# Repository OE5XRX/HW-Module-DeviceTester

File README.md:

# HW-Module-DeviceTester

## License

This project is licensed under [CERN-OHL-S-2.0](https://choosealicense.com/licenses/cern-ohl-s-2.0/).

## Badges

<br>
<br>
<br>
<br>
<br>

## Contact

OE5XRX Amateur Radio Club<br>
🌐 https://oe5xrx.org<br>
✉️ info@oe5xrx.org<br>

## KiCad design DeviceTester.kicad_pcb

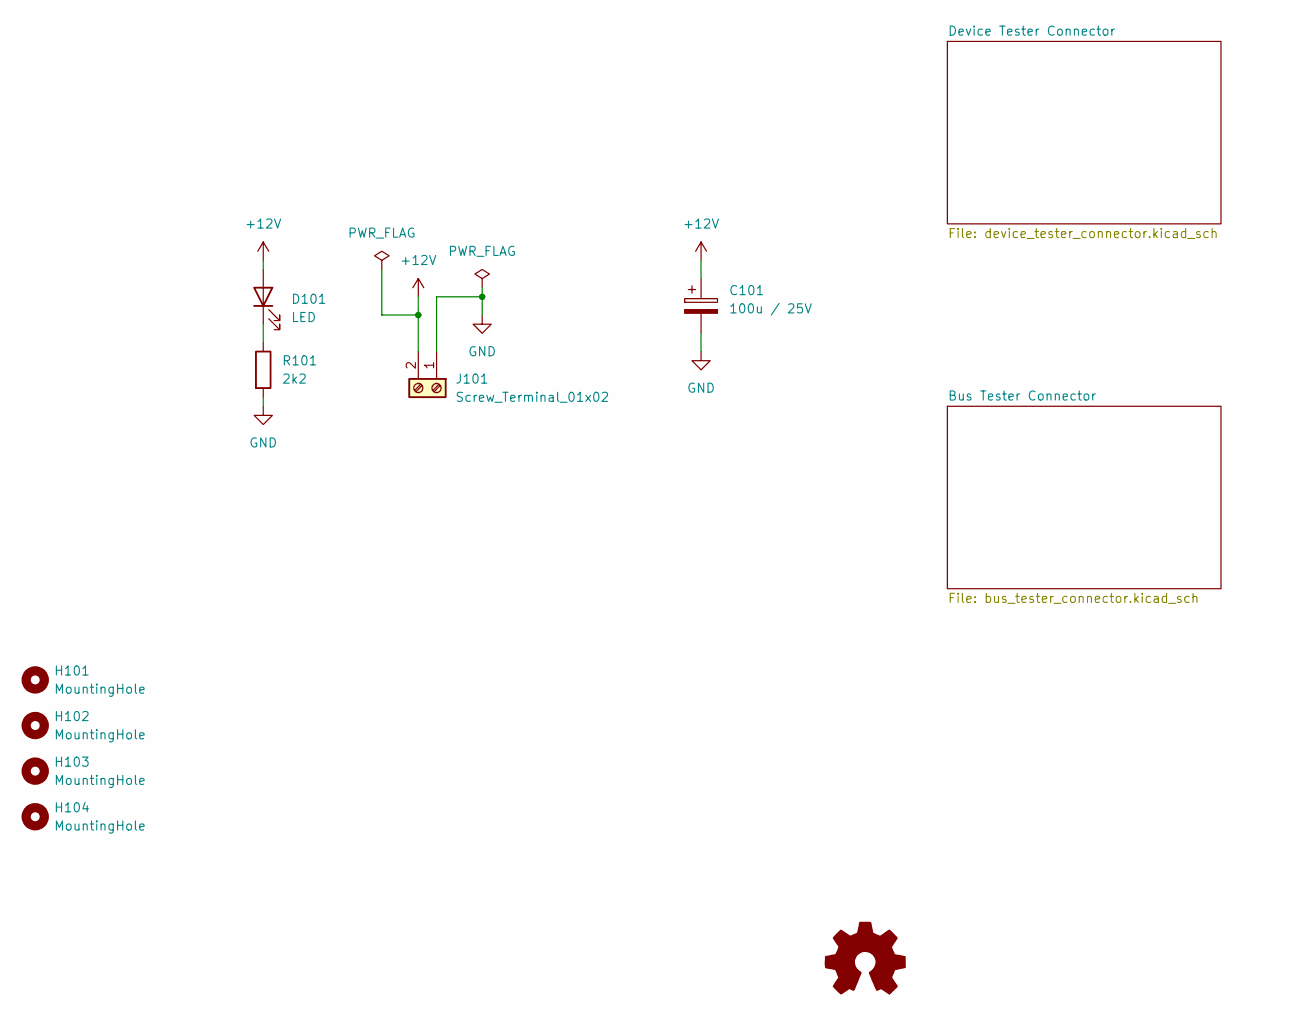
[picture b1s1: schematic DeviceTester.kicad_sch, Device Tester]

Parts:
C101: 100u / 25V; CP_EIA-7343-43_Kemet-X; LCSC C132558
D101: LED; LED_0805_2012Metric; LCSC C84256
H101, H102, H103, H104: MountingHole; MountingHole_3.2mm_M3
J101: Screw_Terminal_01x02; TerminalBlock_Phoenix_MKDS-1,5-2-5.08_1x02_P5.08mm_Horizont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; LCSC C5349557
R101: 2k2; R_0805_2012Metric; LCSC C17520

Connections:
+12V: C101.1, D101.2 (A), J101.2; also elsewhere on the board
GND: C101.2, J101.1, R101.2; also elsewhere on the board
unnamed: D101.1 (K), R101.1

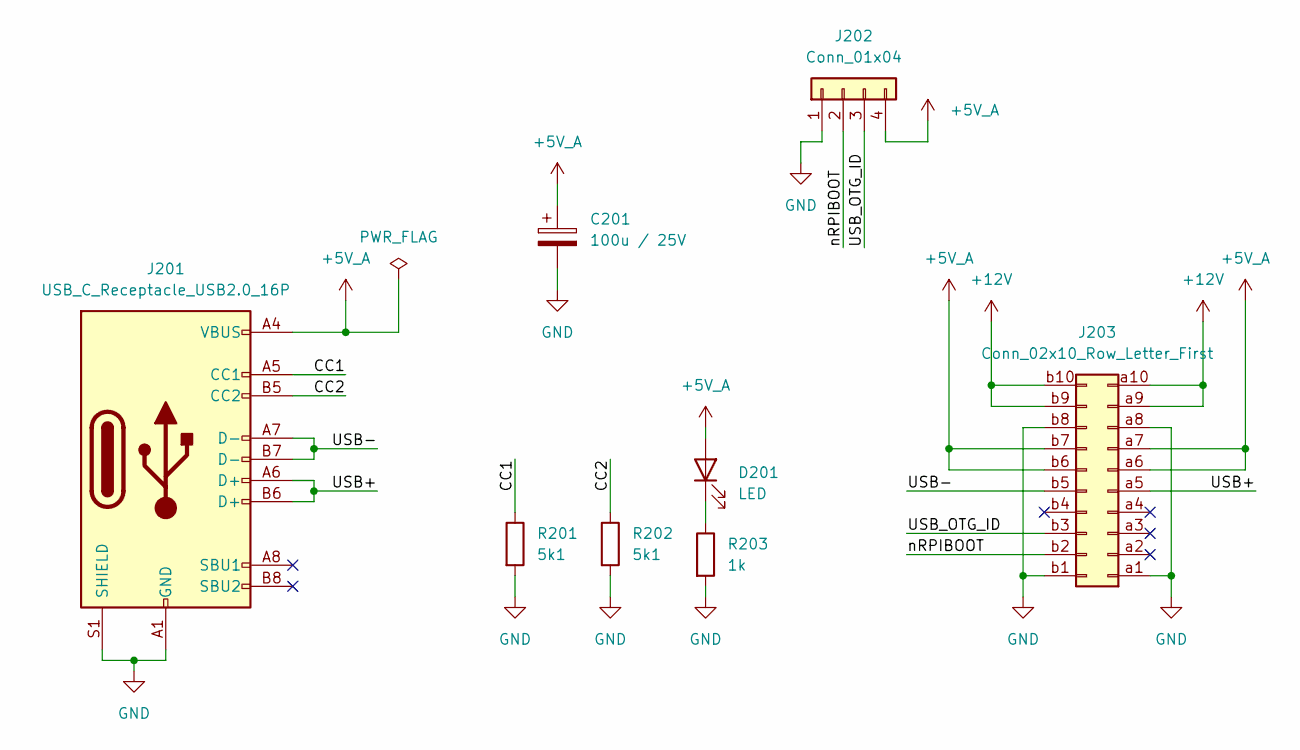
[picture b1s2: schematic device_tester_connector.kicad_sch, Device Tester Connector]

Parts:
C201: 100u / 25V; CP_EIA-7343-43_Kemet-X; LCSC C132558
D201: LED; LED_0805_2012Metric; LCSC C84256
J201: USB_C_Receptacle_USB2.0_16P; USB_C_Receptacle_G-Switch_GT-USB-7010ASV; LCSC C2988369
J202: Conn_01x04; PinHeader_1x04_P2.54mm_Vertical; LCSC C2691448
J203: Conn_02x10_Row_Letter_First; PCN10-20P-2.54DS; MOUSER 798-PCN1020P254DS72
R201, R202: 5k1; R_0805_2012Metric; LCSC C27834
R203: 1k; R_0805_2012Metric; LCSC C17513

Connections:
+5V_A: C201.1, D201.2 (A), J201.A4 (VBUS), J201.A9 (VBUS), J201.B4 (VBUS), J201.B9 (VBUS), J202.4, J203.a6, J203.a7, J203.b6, J203.b7
+12V: J203.a9, J203.a10, J203.b9, J203.b10; also elsewhere on the board
/Device Tester Connector/CC1: J201.A5 (CC1), R201.1
/Device Tester Connector/CC2: J201.B5 (CC2), R202.1
/Device Tester Connector/USB+: J201.A6 (D+), J201.B6 (D+), J203.a5
/Device Tester Connector/USB-: J201.A7 (D-), J201.B7 (D-), J203.b5
/Device Tester Connector/USB_OTG_ID: J202.3, J203.b3
/Device Tester Connector/nRPIBOOT: J202.2, J203.b2
GND: C201.2, J201.A1 (GND), J201.A12 (GND), J201.B1 (GND), J201.B12 (GND), J201.S1 (SHIELD), J202.1, J203.a1, J203.a8, J203.b1, J203.b8, R201.2, R202.2, R203.2; also elsewhere on the board
unnamed: D201.1 (K), R203.1

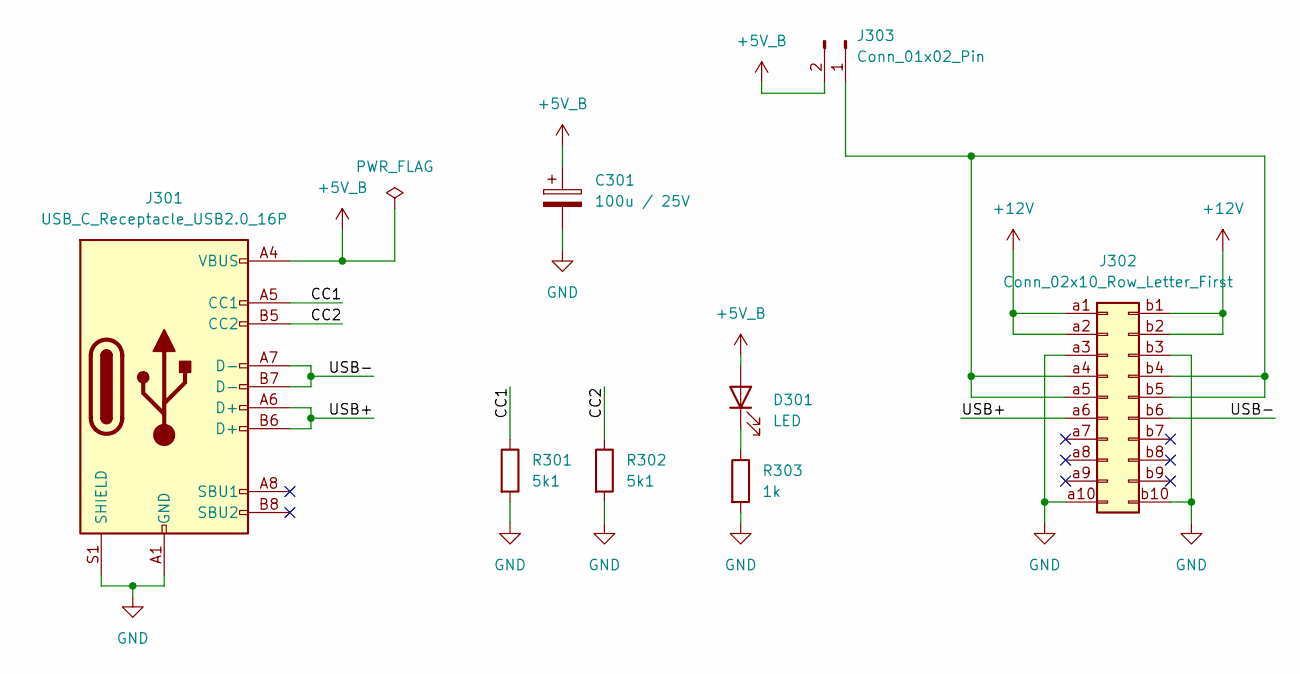
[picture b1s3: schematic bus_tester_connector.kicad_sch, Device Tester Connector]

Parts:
C301: 100u / 25V; CP_EIA-7343-43_Kemet-X; LCSC C132558
D301: LED; LED_0805_2012Metric; LCSC C84256
J301: USB_C_Receptacle_USB2.0_16P; USB_C_Receptacle_G-Switch_GT-USB-7010ASV; LCSC C2988369
J302: Conn_02x10_Row_Letter_First; PCN10C-20S-2.54DS; MOUSER 798-PCN10C20S254DS72
J303: Conn_01x02_Pin; PinHeader_1x02_P2.54mm_Vertical
R301, R302: 5k1; R_0805_2012Metric; LCSC C27834
R303: 1k; R_0805_2012Metric; LCSC C17513

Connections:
+5V_B: C301.1, D301.2 (A), J301.A4 (VBUS), J301.A9 (VBUS), J301.B4 (VBUS), J301.B9 (VBUS), J303.2
+12V: J302.a1, J302.a2, J302.b1, J302.b2; also elsewhere on the board
/Bus Tester Connector/CC1: J301.A5 (CC1), R301.1
/Bus Tester Connector/CC2: J301.B5 (CC2), R302.1
/Bus Tester Connector/USB+: J301.A6 (D+), J301.B6 (D+), J302.a6
/Bus Tester Connector/USB-: J301.A7 (D-), J301.B7 (D-), J302.b6
GND: C301.2, J301.A1 (GND), J301.A12 (GND), J301.B1 (GND), J301.B12 (GND), J301.S1 (SHIELD), J302.a3, J302.a10, J302.b3, J302.b10, R301.2, R302.2, R303.2; also elsewhere on the board
unnamed: D301.1 (K), R303.1
unnamed: J302.a4, J302.a5, J302.b4, J302.b5, J303.1

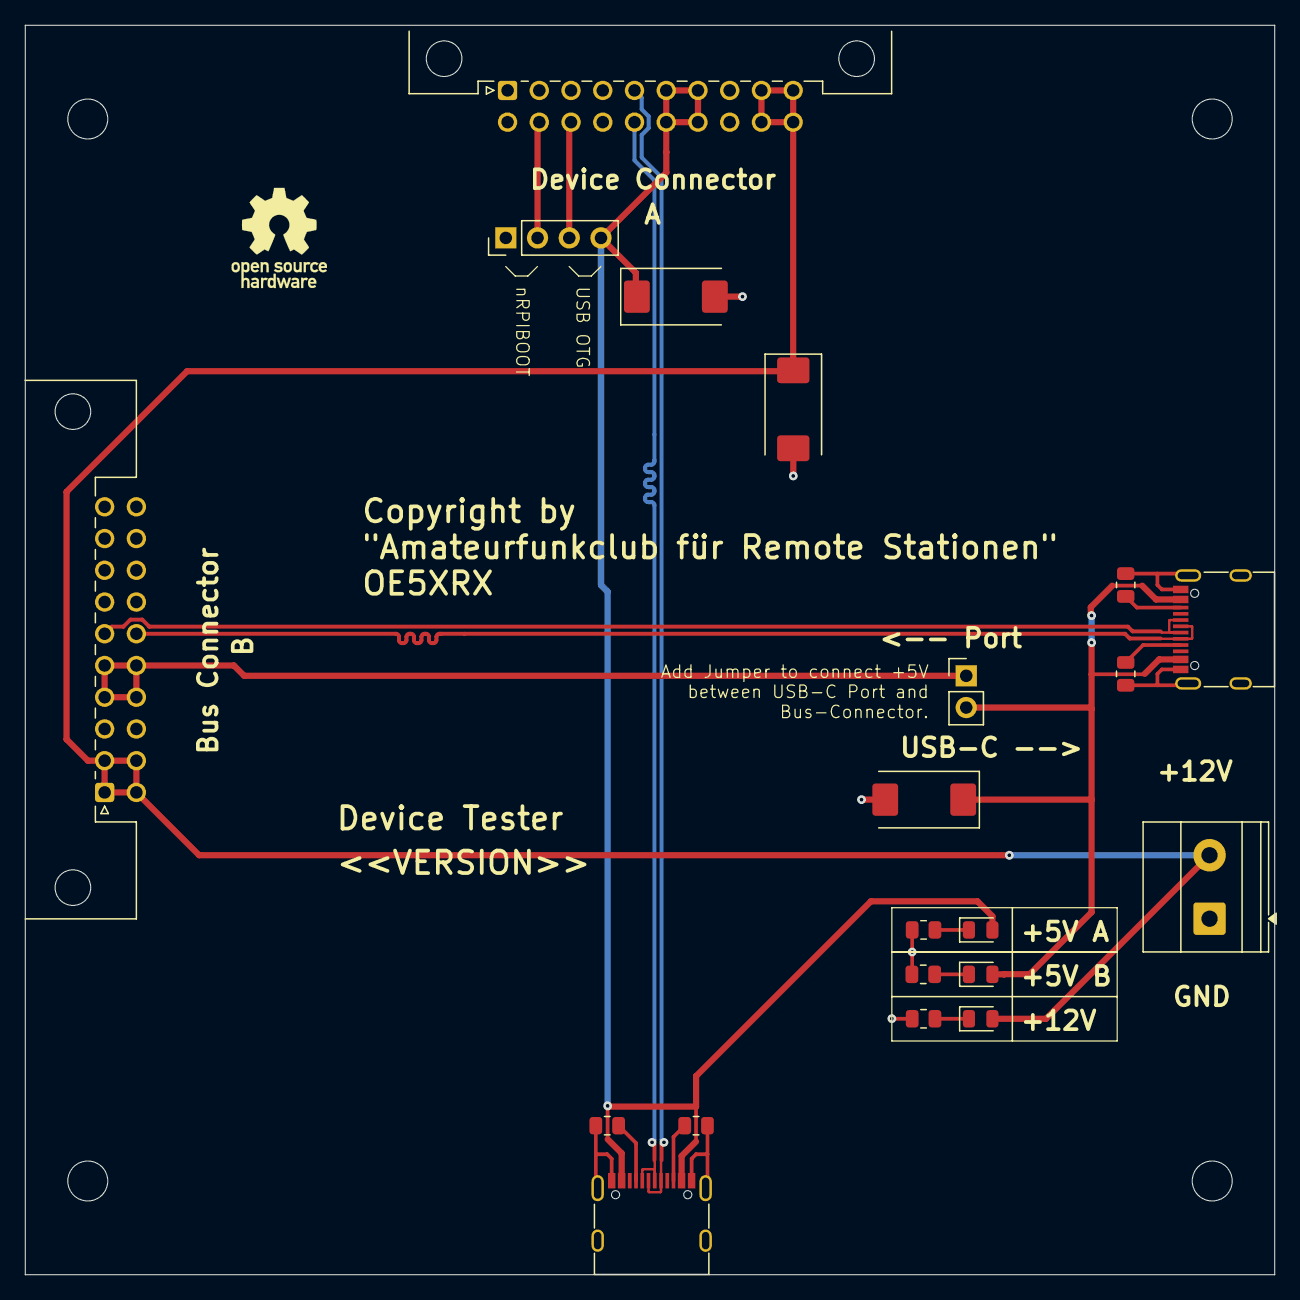
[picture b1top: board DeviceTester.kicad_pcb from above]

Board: 4 copper layers, 100.0 x 100.0 mm, 24 parts (0 on the bottom side), 18 nets.

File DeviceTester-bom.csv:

Row,Description,Part,References,Value,Footprint,Quantity Per PCB,Status,Datasheet,LCSC,MOUSER,Sim.Pins
1,Polarized capacitor,C_Polarized,C101 C201 C301,100u / 25V,CP_EIA-7343-43_Kemet-X,3, ,,C132558,,
2,Light emitting diode,LED,D101 D201 D301,LED,LED_0805_2012Metric,3, ,,C84256,,1=K 2=A
3,"Generic connector, single row, 01x02, script generated",Conn_01x02_Pin,J303,Conn_01x02_Pin,PinHeader_1x02_P2.54mm_Vertical,1, ,,,,
4,"Generic connector, single row, 01x04, script generated (kicad-library-utils/schlib/autogen/connector/)",Conn_01x04,J202,Conn_01x04,PinHeader_1x04_P2.54mm_Vertical,1, ,,C2691448,,
5,"Generic connector, double row, 02x10, row letter first pin numbering scheme (pin number consists of a letter for the row and a number for the pin index in this row. a1, ..., aN; b1, ..., bN), script generated (kicad-library-utils/schlib/autogen/connector/)",Conn_02x10_Row_Letter_First,J203,Conn_02x10_Row_Letter_First,PCN10-20P-2.54DS,1, ,,,798-PCN1020P254DS72,
6,"Generic connector, double row, 02x10, row letter first pin numbering scheme (pin number consists of a letter for the row and a number for the pin index in this row. a1, ..., aN; b1, ..., bN), script generated (kicad-library-utils/schlib/autogen/connector/)",Conn_02x10_Row_Letter_First,J302,Conn_02x10_Row_Letter_First,PCN10C-20S-2.54DS,1, ,,,798-PCN10C20S254DS72,
7,"Generic screw terminal, single row, 01x02, script generated (kicad-library-utils/schlib/autogen/connector/)",Screw_Terminal_01x02,J101,Screw_Terminal_01x02,"TerminalBlock_Phoenix_MKDS-1,5-2-5.08_1x02_P5.08mm_Horizontal",1, ,,C5349557,,
8,USB 2.0-only 16P Type-C Receptacle connector,USB_C_Receptacle_USB2.0_16P,J201 J301,USB_C_Receptacle_USB2.0_16P,USB_C_Receptacle_G-Switch_GT-USB-7010ASV,2, ,https://www.usb.org/sites/default/files/documents/usb_type-c.zip,C2988369,,
9,Resistor,R,R203 R303,1k,R_0805_2012Metric,2, ,,C17513,,
10,Resistor,R,R101,2k2,R_0805_2012Metric,1, ,,C17520,,
11,Resistor,R,R201 R202 R301 R302,5k1,R_0805_2012Metric,4, ,,C27834,,

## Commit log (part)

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2025-08-27 setup project
2025-09-05 🔄 created local 'doc/_config.yml' from remote 'doc/_config.yml'
2025-09-05 🔄 created local 'Gemfile' from remote 'Gemfile'
2025-09-05 🔄 created local 'doc/favicon.ico' from remote 'doc/favicon.ico'
2025-09-05 🔄 synced local '.github/workflows/create-debug-docs.yaml' with remote '.github/workflows/create-debug-docs.yaml'
2025-09-05 Initial gh-pages commit
2025-09-05 Deploying to gh-pages from @ OE5XRX/HW-Module-DeviceTester@580e0a2c611faf02d4cb7a544e7b3e54f748d2d0 🚀
2026-05-12 refactor(ci): replace workflows with HW-Module-CI thin wrappers
2026-05-12 chore(ci): delete files now provided by HW-Module-CI
2026-05-12 feat(docs): migrate index.md to Jekyll Liquid for output paths
2026-05-12 chore: ignore CI-generated doc/_data/project.yml
2026-05-12 rename(kicad): main.kicad_* → DeviceTester.kicad_*
2026-05-12 Deploying to gh-pages from @ OE5XRX/HW-Module-DeviceTester@e64dbdad1d653cdca5ddc9468c192057ce260025 🚀
2026-05-12 Deploying to gh-pages from @ OE5XRX/HW-Module-DeviceTester@7c06aa443cfed3196f16d89867beffe61b42fb91 🚀
2026-05-13 docs: rewrite DeviceTester index.md with full architecture overview
    Adds:
    - 1-sentence description front-matter
    - Übersicht: two-sided board (Device-Tester male PCN10 / Bus-Tester
    female PCN10C) + 3 power rails + flash header for rpiboot
    - Mermaid block diagram showing both halves + flash header + DUT/BB
    - Steckverbinder-Tabelle: all 7 J-refs (Phoenix, 2× USB-C, 4-pin Flash,
2026-05-13 Deploying to gh-pages from @ OE5XRX/HW-Module-DeviceTester@2080303631b8d92fb2f0abd11e85753ca4c65cf4 🚀
2026-05-15 Deploying to gh-pages from @ OE5XRX/HW-Module-DeviceTester@d42569cc7f7d62645c0844f2c0b1aef27dd5d257 🚀
2026-05-15 Deploying to gh-pages from @ OE5XRX/HW-Module-DeviceTester@42c10af0a1778cd27d6dd8501a3ea21b23330269 🚀

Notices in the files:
DeviceTester.kicad_pcb:
Copyright by
{dblquote}Amateurfunkclub für Remote Stationen{dblquote}
README.md:
License: CERN-OHL-S
